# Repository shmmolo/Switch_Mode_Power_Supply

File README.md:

# 25 W @ 9 V Flyback SMPS Charger with USB-PD

A compact isolated Flyback SMPS delivering 25 W power for USB-C PD fast charging, designed around TI’s UCC28750 controller.

## Features
- 220 VAC input → 9 V / 5 V output
- USB-PD communication via IP2721
- UCC28750 PWM controller + optocoupler feedback
- Schottky rectification and snubber protection
- 2-layer PCB with ground plane and isolation gap

## Components
- **U1:** UCC28750 Flyback Controller  
- **Q1:** NMOS primary switch  
- **U2:** PC817 Optocoupler  
- **U3:** TL431 Voltage Reference  
- **U4:** IP2721 USB-PD Controller  
- **D1–D5:** GBU4K + SS310 Schottky diodes  
- **T1:** Flyback Transformer (custom)  
- **C1–C12:** Filtering capacitors

## Output Specs
| Mode | Voltage | Current | Power |
|------|----------|----------|--------|
| Default | 5 V | 2.8 A | 14 W |
| USB-PD | 9 V | 2.8 A | 25 W |

## Notes
PCB under layout stage – final design will feature 2-layer structure with dedicated GND plane, thermal reliefs, and isolation.

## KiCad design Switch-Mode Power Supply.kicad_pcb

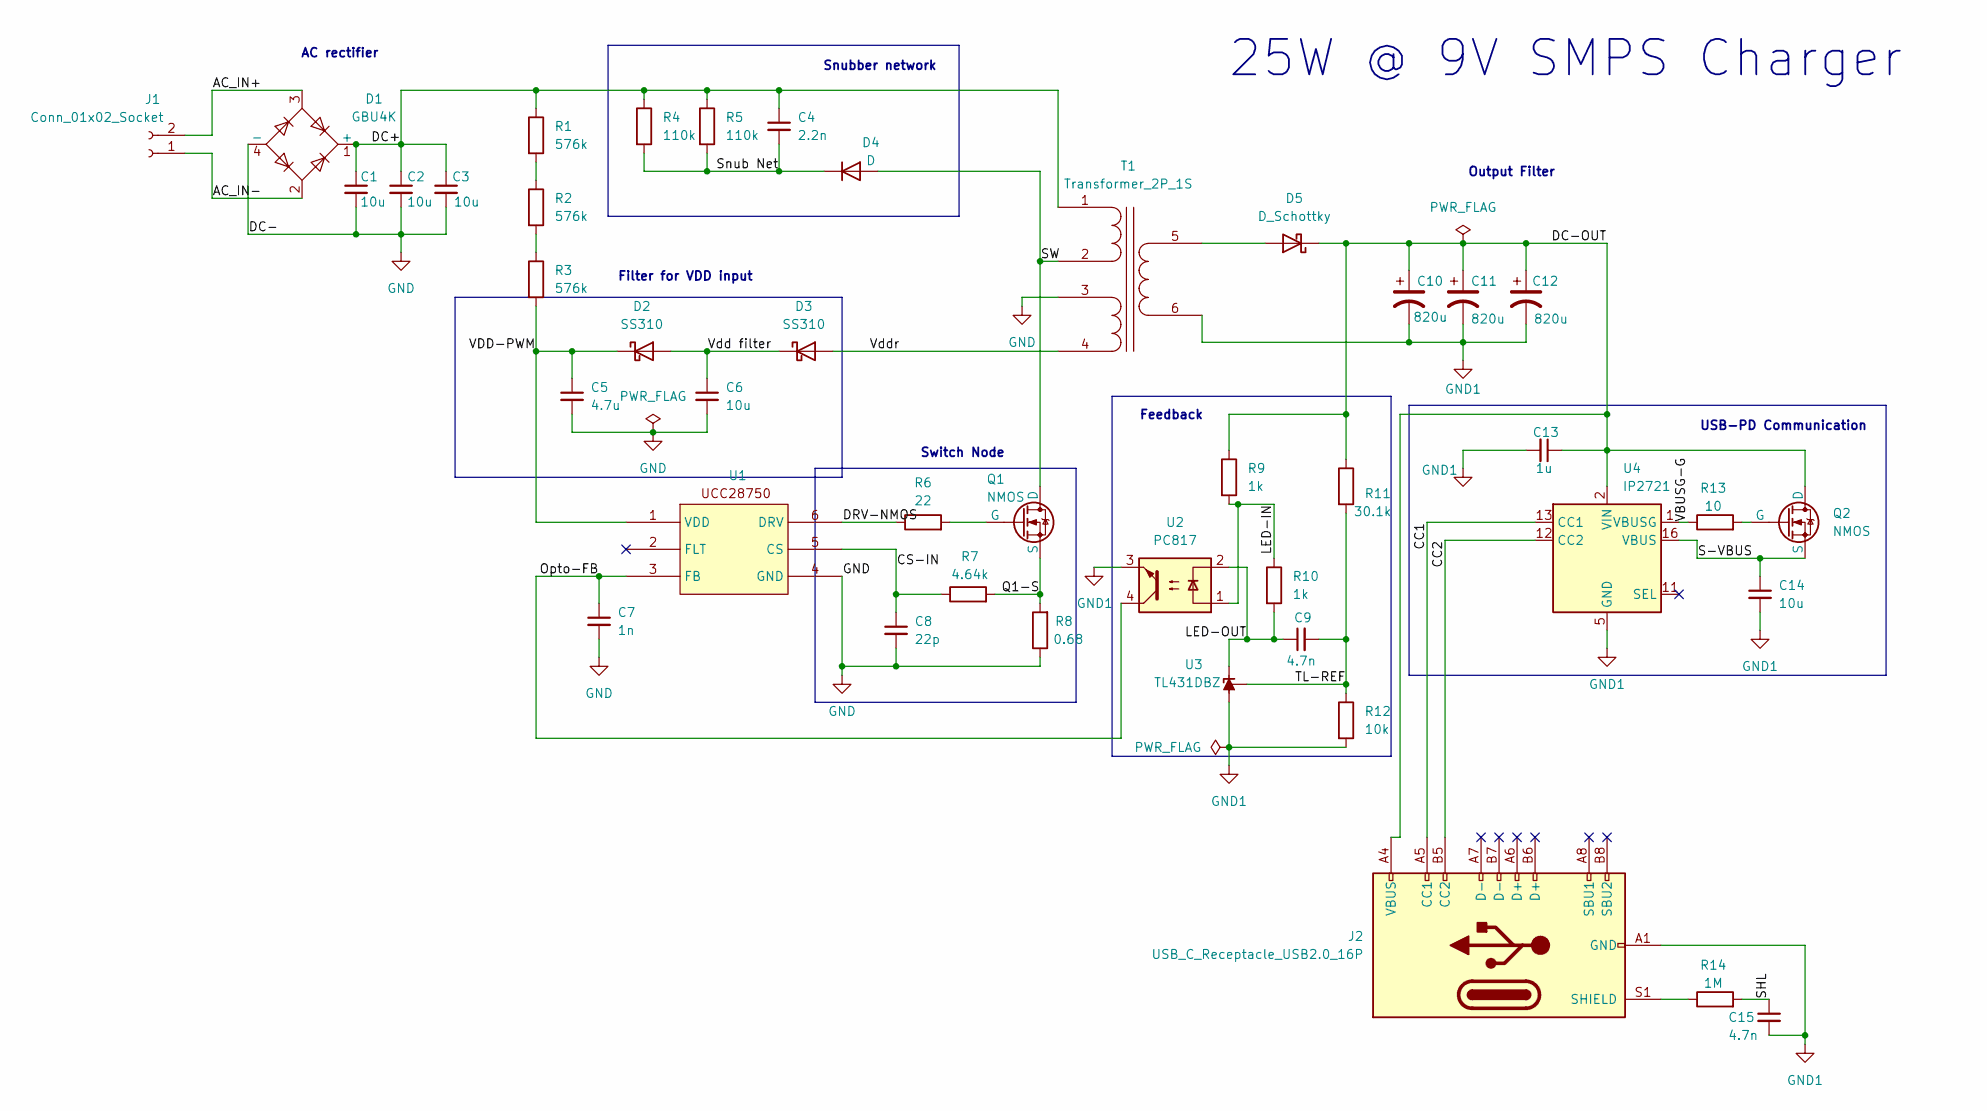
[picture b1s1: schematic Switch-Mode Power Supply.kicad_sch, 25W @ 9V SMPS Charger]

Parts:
C1, C2, C3: 10u; CP_Radial_D10.0mm_P5.00mm
C4: 2.2n; C_1206_3216Metric_Pad1.33x1.80mm_HandSolder
C5: 4.7u; C_1206_3216Metric_Pad1.33x1.80mm_HandSolder
C6, C14: 10u; C_1206_3216Metric_Pad1.33x1.80mm_HandSolder
C7: 1n; C_1206_3216Metric_Pad1.33x1.80mm_HandSolder
C8: 22p; C_1206_3216Metric_Pad1.33x1.80mm_HandSolder
C9, C15: 4.7n; C_1206_3216Metric_Pad1.33x1.80mm_HandSolder
C10, C11, C12: 820u; CP_Elec_4x5.4
C13: 1u; C_1206_3216Metric_Pad1.33x1.80mm_HandSolder
D1: GBU4K; Diode_Bridge_Vishay_GBU
D2, D3: SS310; D_SMA
D4: D; D_SMA
D5: D_Schottky; D_SMB_Handsoldering
J1: Conn_01x02_Socket; TerminalBlock_Phoenix_MKDS-1,5-2_1x02_P5.00mm_Horizontal
J2: USB_C_Receptacle_USB2.0_16P; USB_C_Receptacle_HRO_TYPE-C-31-M-12
Q1, Q2: NMOS; TO-252-3_TabPin2
R1, R2, R3: 576k; R_1210_3225Metric_Pad1.30x2.65mm_HandSolder
R4, R5: 110k; R_2010_5025Metric_Pad1.40x2.65mm_HandSolder
R6: 22; R_1210_3225Metric_Pad1.30x2.65mm_HandSolder
R7: 4.64k; R_1210_3225Metric_Pad1.30x2.65mm_HandSolder
R8: 0.68; R_2010_5025Metric_Pad1.40x2.65mm_HandSolder
R9, R10: 1k; R_1210_3225Metric_Pad1.30x2.65mm_HandSolder
R11: 30.1k; R_1210_3225Metric_Pad1.30x2.65mm_HandSolder
R12: 10k; R_1210_3225Metric_Pad1.30x2.65mm_HandSolder
R13: 10; R_1210_3225Metric_Pad1.30x2.65mm_HandSolder
R14: 1M; R_1210_3225Metric_Pad1.30x2.65mm_HandSolder
T1: Transformer_2P_1S; B66417G0000X149
U1: SOT-23-6
U2: PC817; DIP-4_W7.62mm
U3: TL431DBZ; SOT-23
U4: IP2721; TSSOP-16_4.4x5mm_P0.65mm

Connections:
/AC_IN+: D1.3, J1.2
/AC_IN-: D1.2, J1.1
/CC1: J2.A5 (CC1), U4.13 (CC1)
/CC2: J2.B5 (CC2), U4.12 (CC2)
/CS-IN: C8.1, R7.1, U1.5 (CS)
/DC+: C1.1, C2.1, C3.1, C4.1, D1.1 (+), R1.1, R4.1, R5.1, T1.1
/DC-OUT: C10.1, C11.1, C12.1, C13.1, D5.1 (K), J2.A4 (VBUS), J2.A9 (VBUS), J2.B4 (VBUS), J2.B9 (VBUS), Q2.1 (D), R9.1, R11.1, U4.2 (VIN)
/DRV-NMOS: R6.1, U1.6 (DRV)
/LED-IN: R9.2, R10.1, U2.1
/LED-OUT: C9.1, R10.2, U2.2, U3.1 (K)
/Opto-FB: C7.1, U1.3 (FB), U2.4
/Q1-S: Q1.3 (S), R7.2, R8.2
/S-VBUS: C14.1, Q2.3 (S), U4.16 (VBUS)
/SHL: C15.1, R14.2
/SW: D4.2 (A), Q1.1 (D), T1.2
/Snub Net: C4.2, D4.1 (K), R4.2, R5.2
/TL-REF: C9.2, R11.2, R12.1, U3.2 (REF)
/VBUSG-G: R13.1, U4.1 (VBUSG)
/VDD-PWM: C5.1, D2.1 (K), R3.2, U1.1 (VDD)
/Vdd filter: C6.1, D2.2 (A), D3.1 (K)
/Vddr: D3.2 (A), T1.4 (AUX2)
GND: C1.2, C2.2, C3.2, C5.2, C6.2, C7.2, C8.2, D1.4 (-), R8.1, T1.3 (AUX1), U1.4 (GND)
GND1: C10.2, C11.2, C12.2, C13.2, C14.2, C15.2, J2.A1 (GND), J2.A12 (GND), J2.B1 (GND), J2.B12 (GND), R12.2, T1.6 (S2), U2.3, U3.3 (A), U4.5 (GND)
unnamed: D5.2 (A), T1.5 (S1)
unnamed: J2.S1 (SHIELD), R14.1
unnamed: Q1.2 (G), R6.2
unnamed: Q2.2 (G), R13.2
unnamed: R1.2, R2.1
unnamed: R2.2, R3.1

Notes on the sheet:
AC rectifier
Output Filter
Feedback
Snubber network
Switch Node
USB-PD Communication
25W @ 9V SMPS Charger
Filter for VDD input

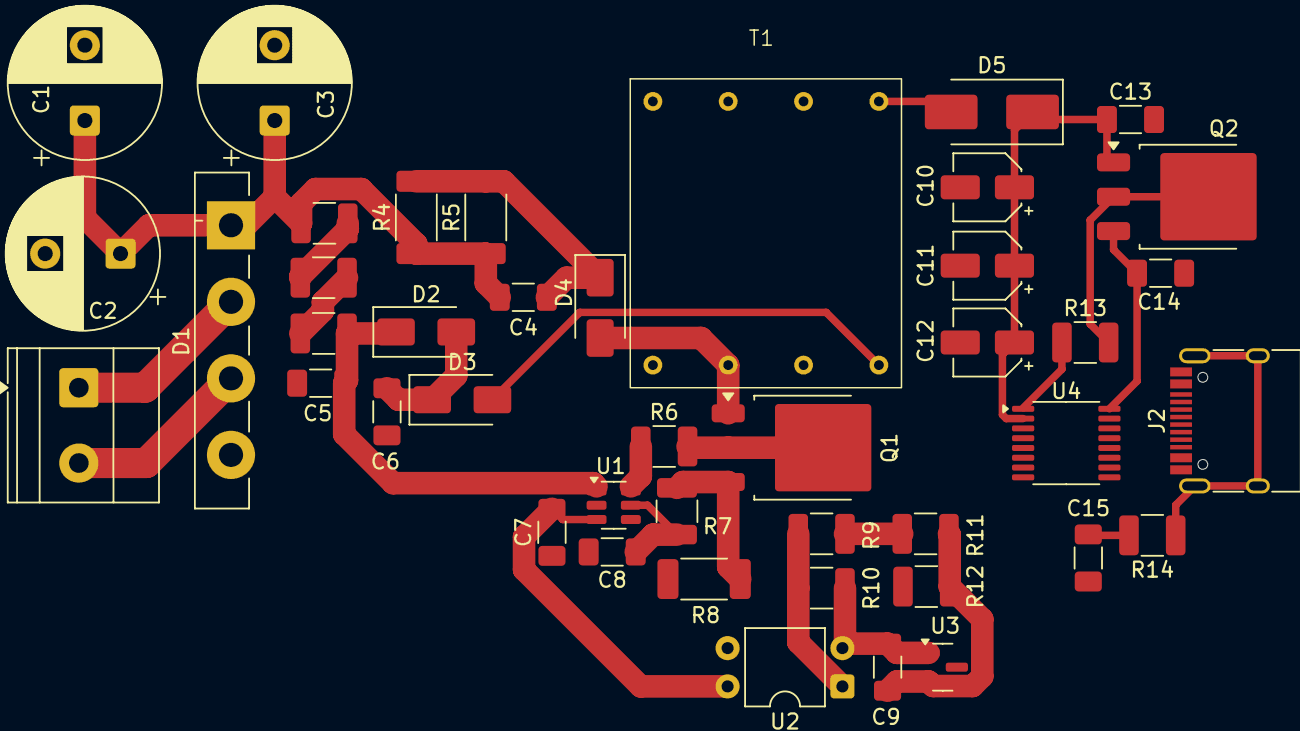
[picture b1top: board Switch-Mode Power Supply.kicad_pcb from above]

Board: 2 copper layers, 43 parts (0 on the bottom side), 29 nets.

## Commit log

2025-10-29 README.md
2025-10-29 SMPS.kicad_sch
2025-10-29 Delete
2025-10-29 Added to Hardware
2025-10-29 Added to Docs
